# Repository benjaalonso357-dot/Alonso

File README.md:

# Alonso
La carpeta buzo contiene la carpeta `.history`, varias carpetas de respaldo llamadas `_restore_backup_...`, la carpeta `ProyectoFinalRossiPuto`, el archivo de la placa electrónica de KiCad (`buzo.kicad_pcb`), el archivo de configuración local (`buzo.kicad_prl`), el archivo del proyecto (`buzo.kicad_pro`), el esquema eléctrico (`buzo.kicad_sch`) y varios archivos Gerber (`buzo-B_Cu.gbr`, `buzo-F_Cu.gbr`, `buzo-B_Mask.gbr`, `buzo-F_Mask.gbr`, `buzo-B_Silkscreen.gbr`, `buzo-F_Silkscreen.gbr` y `buzo-Edge_Cuts.gbr`), además del archivo `buzo-job.gbrjob`, que contiene información para la fabricación de la placa.

La carpeta Nueva carpeta contiene el archivo `jaja-drl.rpt`, que es un informe relacionado con las perforaciones de la placa electrónica.

La carpeta prueba del proyecto contiene el archivo temporal `~prueba del proyecto.kicad_sch.lck`, el archivo de configuración local `prueba del proyecto.kicad_prl`, el archivo de configuración del proyecto `prueba del proyecto.kicad_pro` y el esquema eléctrico `prueba del proyecto.kicad_sch`. Estos archivos corresponden a una versión de prueba del diseño realizado en KiCad.

La carpeta sketch_oct23a contiene el archivo `sketch_oct23a.ino`, que es el código fuente de Arduino donde se escriben las instrucciones para controlar los componentes electrónicos del proyecto.

El archivo README contiene información general e instrucciones sobre el proyecto, y sirve para explicar su contenido y facilitar que otras personas puedan entenderlo.

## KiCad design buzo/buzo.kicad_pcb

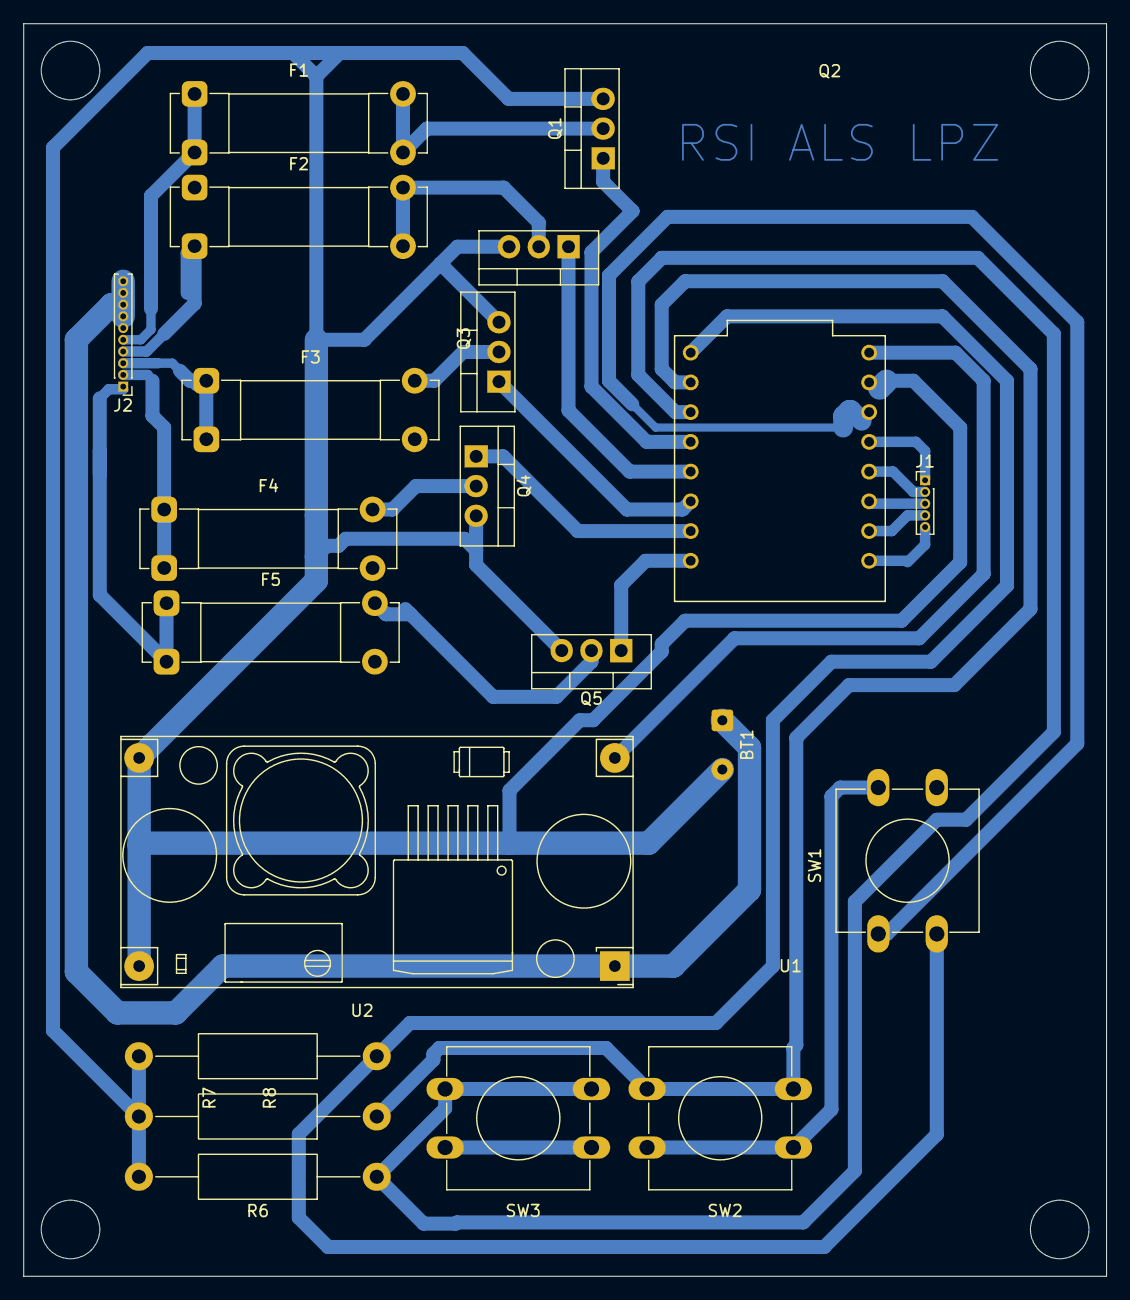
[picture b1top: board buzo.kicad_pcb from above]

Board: 2 copper layers, 92.5 x 107.0 mm, 21 parts (0 on the bottom side), 27 nets.

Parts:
BT1: Battery; SolderWire-0.25sqmm_1x02_P4.2mm_D0.65mm_OD1.7mm
F1, F2, F3, F4, F5: 1A; Fuseholder_Clip-5x20mm_Bel_FC-203-22_Lateral_P17.80x5.00mm_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
J1: Conn_01x05_Socket; PinHeader_1x05_P1.00mm_Vertical
J2: Conn_01x10_Socket; PinHeader_1x10_P1.00mm_Vertical
Q1, Q2, Q3, Q4, Q5: IRF3205; TO-220-3_Vertical
R6, R7, R8: 1k; R_Axial_DIN0411_L9.9mm_D3.6mm_P20.32mm_Horizontal
SW1, SW2, SW3: SW_Push; SW_PUSH-12mm
U1: ESP32-C3_SUPERMINI_TH; MODULE_ESP32-C3_SUPERMINI_TH
U2: LM2596S-5; YAAJ_DCDC_StepDown_LM2596

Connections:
unnamed: BT1.1 (+), J2.6, J2.7, J2.8, J2.9, J2.10, U2.1 (VIN)
unnamed: BT1.2 (-), Q1.3 (S), Q2.3 (S), Q3.3 (S), Q4.3 (S), Q5.3 (S), R6.2, R7.2, R8.2, U2.3 (GND), U2.4 (FB)
unnamed: J1.1, U1.4 (GPIO4)
unnamed: J1.2, U1.3 (GPIO3)
unnamed: J1.3, U1.2 (GPIO2)
unnamed: J1.4, U1.1 (GPIO1)
unnamed: J1.5, U1.0 (GPIO0)
unnamed: F5.1, J2.1
unnamed: F4.1, J2.2
unnamed: F3.1, J2.3
unnamed: F2.1, J2.4
unnamed: F1.1, J2.5
unnamed: F1.2, Q1.2 (D)
unnamed: Q1.1 (G), U1.8 (GPIO8)
unnamed: F2.2, Q2.2 (D)
unnamed: Q2.1 (G), U1.9 (GPIO9)
unnamed: F3.2, Q3.2 (D)
unnamed: Q3.1 (G), U1.10 (GPIO10)
unnamed: F4.2, Q4.2 (D)
unnamed: Q4.1 (G), U1.20 (GPIO20)
unnamed: F5.2, Q5.2 (D)
unnamed: Q5.1 (G), U1.21 (GPIO21)
unnamed: SW1.1, SW2.1, SW3.1
unnamed: R8.1, SW1.2, U1.5 (GPIO5)
unnamed: R7.1, SW2.2, U1.6 (GPIO6)
unnamed: R6.1, SW3.2, U1.7 (GPIO7)
unnamed: U1.5V, U2.2 (OUT)
